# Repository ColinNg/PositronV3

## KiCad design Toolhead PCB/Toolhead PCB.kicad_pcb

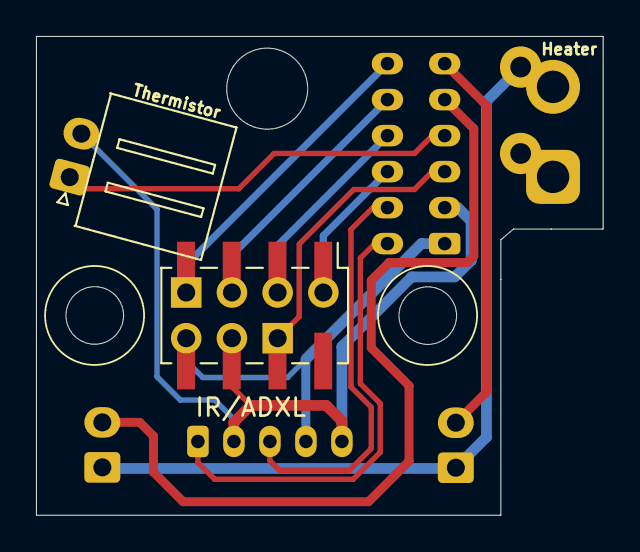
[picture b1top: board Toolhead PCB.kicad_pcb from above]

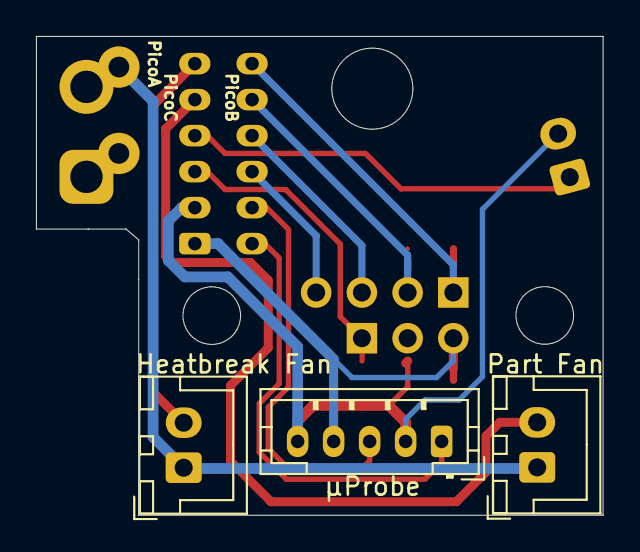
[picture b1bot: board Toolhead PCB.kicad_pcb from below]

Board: 2 copper layers, 31.5 x 26.6 mm, 12 parts (6 on the bottom side), 14 nets.

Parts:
Hole: Hole 3.2mm; MountingHole_3.2mm_M3
Hole#2: Capacitor Hole 4.5mm; MountingHole_4.5mm
Hole#3: Hole 3.2mm; MountingHole_3.2mm_M3
J1: PicoA; SolderWire-0.5sqmm_1x02_P4.8mm_D0.9mm_OD2.3mm
J2: PicoB; JST_PH_B6B-PH-K_1x06_P2.00mm_Vertical
J3: PicoC; JST_PH_B6B-PH-K_1x06_P2.00mm_Vertical
J4: Heater; AMASS_XT30UPB-M_1x02_P5.0mm_Vertical
J5: Thermistor; JST_XH_S2B-XH-A_1x02_P2.50mm_Horizontal
J6: Heatbreak Fan; JST_XH_B2B-XH-A_1x02_P2.50mm_Vertical
J7: Part Fan; JST_XH_B2B-XH-A_1x02_P2.50mm_Vertical
J8: IR/ADXL; Muon 3D IR Bed Probe with ADXL345
J9: µProbe; JST_PH_B5B-PH-K_1x05_P2.00mm_Vertical

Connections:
/5V: J3.1, J8.3 (V), J9.4
/+24V: J1.2, J4.2, J6.1, J7.1
/CS: J2.6, J8.4 (CS)
/FAN2- Heatbreak: J3.6, J6.2
/FAN3- Part: J3.5, J7.2
/GND: J3.2, J5.2, J8.2 (G), J9.2, J9.5
/Heater-: J1.1, J4.1
/MI: J2.5, J8.5 (MI)
/MO: J2.4, J8.6 (MO)
/SC: J2.3, J8.7 (SC)
/Servo: J2.2, J9.3
/TH0+: J3.4, J5.1
/Z-Stop: J3.3, J8.1 (O)
/µProbe: J2.1, J9.1

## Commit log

2023-12-30 Parametric Synchromesh Drive Pulley by Qiblical on Thingiverse: https://www.thingiverse.com/thing:5427806
2023-12-30 3D_printed_toolhead_interconnect_fixed.stl from Sample Name, Discord, 2022-10-20 07:57 https://discord.com/channels/977582747939897344/977582937853808730/1032668809204617317
2023-12-30 Remove image of unintentional holes
2023-12-30 The two transparent light covers converted to .stl so I can attempt to 3D print them, since Funssor provided only the Black Acrylic Panel Parts.
2025-05-02 Fix typo in name
2025-09-10 Initial commit of schematic for JourneyMaker Toolhead PCB: - J1 Amass XT30PW-M from SKR Pico for Hot End Heater - J2 JST PH 2.0 6-pin from SKR Pico for Muon IR Bed Probe and Fans - J3 JST PH 2.0 6-pi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
2025-09-10 Schematic and PCB for JourneyMaker Toolhead PCB: - J1 Soldered wires from SKR Pico for Hot End Heater - J2 JST PH 2.0 6-pin from SKR Pico for BQ MicroProbe and Muon IR Probe's ADXL345 - J3 JST PH 2.0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
2025-09-10 Used wider traces for heater, fans, thermistor, microprobe power, etc.
2025-09-10 Combine a through-hole and an SMD connector to get the passthrough holes and vias.
2025-09-10 JST connectors are soldered to the back: added 8 vias for signal and 2 vias for fan power. Added mounting holes (but have not resolved clearances).
2025-09-11 Holes for mounting. Moved traces to avoid holes. Moved most vias to the large pads. Changed the ADXLL345 wire order so it would route better. Made Schematic match PCB.
2025-09-11 Thicker traces for heater, fans, and shared ground or power.
2025-09-11 Changed vias to 0.75mm to match through hole components, avoiding one tool change.
2025-09-11 Shortened label on IR+ADXL345 --> IR/ADXL Set the IR/ADXL header to Do Not Populate, and Exclude from BOM
2025-09-19 Toolhead PCB: Exported Excellon Drill Files and Gerbers
2025-09-19 Toolhead_3x3010_v16.rar
2025-09-19 Toolhead_LT_v2_v30.7z (Positron LT Project)
2025-09-19 Positron test hotend shroud ElevatedisScout 1.7z
2025-09-24 Changed XT30 footprint from `Connector_AMASS:AMASS_XT30PW-F_1x02_P2.50mm_Horizontal` to `Connector_AMASS:AMASS_XT30UPB-F_1x02_P5.0mm_Vertical` so there would not be the extra pads and drills for the 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
2025-09-24 Remove unused files (Gerber X2 Drill don't seem to work).
2025-09-24 Added 3 fake vias so we could get them drilled out in FlatCAM.
2025-09-24 Basic FlatCAM with B_Cu.gbr, Edge_Cuts.gbr, and PTH.drl mirrored along X axis of Edge_Cuts.gbr. Added Alignment Drills.
2025-09-24 I'm able to save the CNC Jobs for drilling without corrupting the Toolhead PCB-PTH.drl data.
2025-09-24 Toohead PCB FlatCAM CNC Jobs.7z
2025-09-25 An ok profile file.
2025-09-25 Toolhead PCB FlatCAM CNC Jobs
2025-09-25 Changed via holes that were 0.3mm to 0.75mm for easier manufacturing.
2025-09-25 Basic FlatCAM with B_Cu.gbr, Edge_Cuts.gbr, and PTH.drl mirrored along X axis of Edge_Cuts.gbr. Added Alignment Holes. Set Origin.
2025-09-25 It recalculated all the fills when I generated new Gerbers.
2025-09-25 Changed Alignment Drills to use a 2.4mm Corn Cob bit.
2025-09-26 Change the V-bit tip diameter to 0.1 so the FlatCAM geometry actually isolates the traces. Regenerated `03 Bottom Copper.nc`
2025-09-26 Moved the hole for the capacitor down by 0.4mm, and enlarged diameter by 0.5mm. Updated Edge Cuts circle to match. Exported Gerbers and Excellon files. Basic FlatCAM with B_Cu.gbr, Edge_Cuts.gbr, and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
2025-09-26 Changed Mill Holes and Cutout to use a 2.0mm Upcut Conical Endmill.
2025-09-29 Created symbol and footprint for the Muon 3D IR Bed Probe with ADXL345.
2025-09-29 Labeled all the pins/nets. Moved connector Values to F.Silkscreen and moved connector References to F.Fab.
2025-09-30 Redesigned PCB: - narrower so it does not protrude as much past the boundary when the Positron is packed for storage - all traces on front side only (no more manually soldered vias); still recommend 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
2025-09-30 Basic FlatCAM with B_Cu.gbr, Edge_Cuts.gbr, NPTH.drl, and PTH.drl mirrored along X axis of Edge_Cuts.gbr. Added Alignment Holes. Set Origin.
2025-09-30 Move alignment holes. Renamed .nc files with `E3-175` for Endmill 3.175mm.
2025-09-30 Changed Silkscreen labels.
2025-10-01 Widened traces to tolerate overmilling.
2025-10-01 Regenerated CNC Jobs, adding a Realignment job in case I want to use the same holes in the spoilboard to make another PCB.
2025-10-03 Regenerated CNC Jobs for spindle speed 10,000.
2025-10-03 Schematic more closely matches traces. Updated PicoB and PicoC wiring harnesses: flagged as non populated and deleted silkscreen. Removed pins from Muon 3D IR Bed Probe with ADXL345. Moved traces fro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
2025-10-08 Changed V-bit to 15° 0.1mm. Changed order of milling (mill the Top Copper first, after it succeeds mill the alignment holes). Changed Endmill to 2.0mm.
2025-10-10 The 0.75mm holes do not retain the Silicone 28AWG Ribbon Cable wires properly, so the Schematic and PCB use a new footprint `SolderWire-0.1sqmm_1x06_P2.0mm_D0.4mm_OD1mm.kicad_mod` which has the same 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
2025-10-10 Regenerated CNC Jobs.
2025-11-05 Duplicated the `Toolhead PCB` folder to `Toolhead PCB CNC`.
2025-11-05 [2025-10-03] Moved most power traces to the back so I they could be wider while the board got narrower on the right side.
2025-11-05 [2025-10-03] Gerbers submitted to JLCPCB.
